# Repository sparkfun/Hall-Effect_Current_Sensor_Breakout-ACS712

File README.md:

SparkFun Current Sensor Breakout - ACS723
=====================================================

[*SparkFun Current Sensor Breakout - ACS723 (SEN-13679)*](https://www.sparkfun.com/products/13679)

This is a breakout board for the fully integrated Hall Effect based linear ACS723 current sensor. 
The sensor gives precise current measurement for both AC and DC signals.

Repository Contents
-------------------
* **/Hardware** - All Eagle design files (.brd, .sch)
* **/Production** - Production .brd files

Documentation
-------------------
[Hookup Guide](https://learn.sparkfun.com/tutorials/current-sensor-breakout-acs723-hookup-guide) - Basic hookup guide for the ACS723 Current Sensor Breakout.

Product Versions
----------------
* [SEN-13679](https://www.sparkfun.com/products/13679)- Current ACS723 Version of this Board
* [SEN-08882 (RETIRED)](https://github.com/sparkfun/Hall-Effect_Current_Sensor_Breakout-ACS712)- Initial release; ACS712 Version of this Board

License Information
-------------------

This product is _**open source**_! 

Please review the LICENSE.md file for license information. 

If you have any questions or concerns on licensing, please contact techsupport@sparkfun.com.

Distributed as-is; no warranty is given.

- Your friends at SparkFun.

_<COLLABORATION CREDIT>_

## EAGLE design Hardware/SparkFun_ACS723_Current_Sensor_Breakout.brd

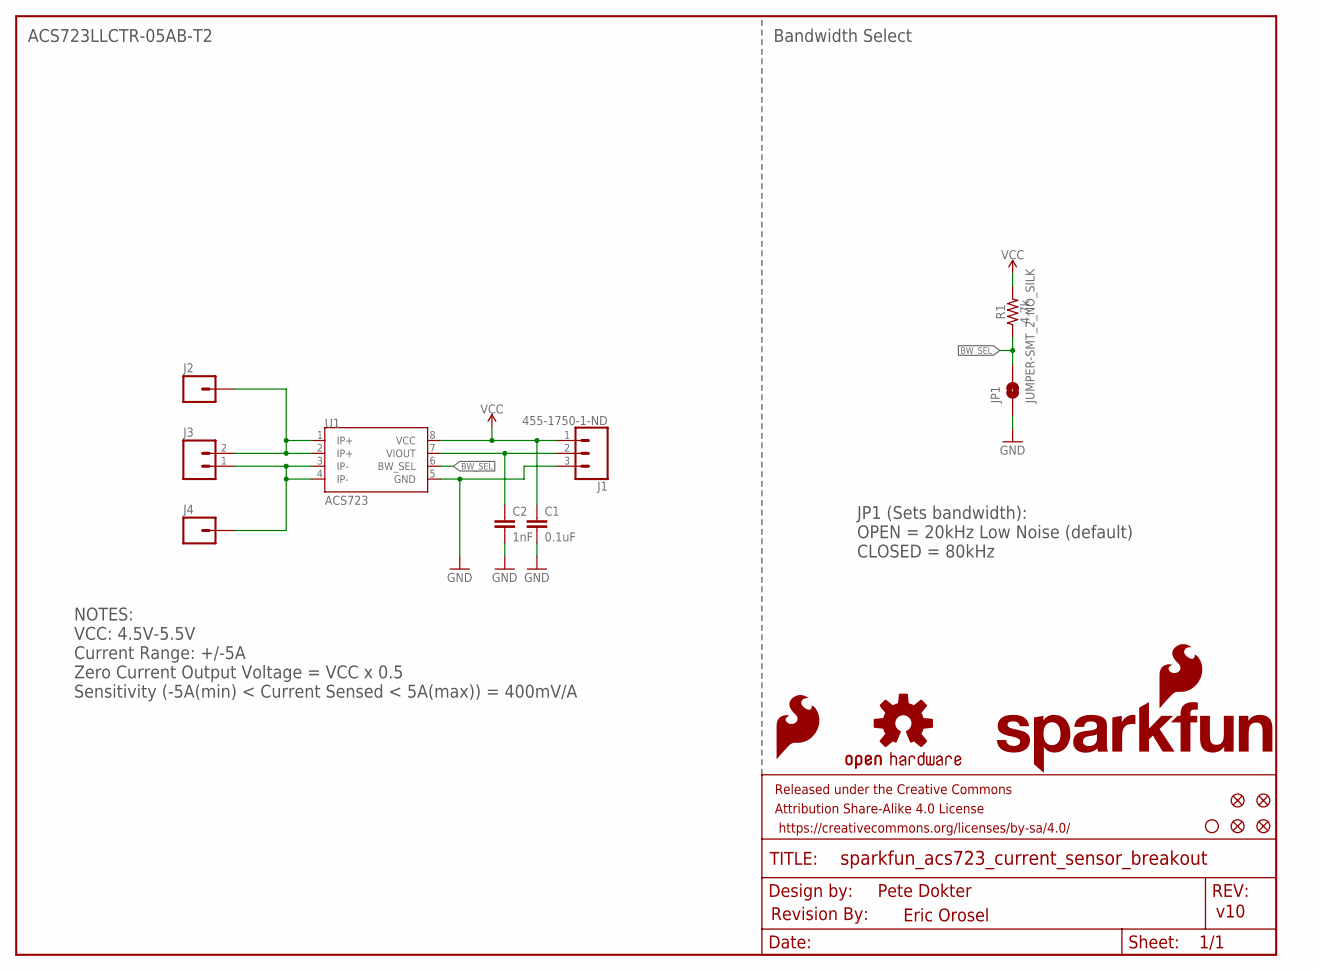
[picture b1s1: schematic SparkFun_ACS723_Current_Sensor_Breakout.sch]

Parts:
C1: 0.1uF; 0603
C2: 1nF; 0603
FD2, FD3, FD4, FD5: FIDUCIAL1X2; FIDUCIAL-1X2
FRAME1: FRAME-LETTER; CREATIVE_COMMONS
J1: 455-1750-1-ND; 1X03
J2, J4: M01-SMTSO-256-ET; SMTSO-256-ET
J3: M021X02_NO_SILK; 1X02_NO_SILK@1
JP1: JUMPER-SMT_2_NO_SILK; SMT-JUMPER_2_NO_SILK
JP3: STAND-OFFTIGHT; STAND-OFF-TIGHT
LOGO1: SFE_LOGO_FLAME.1_INCH; SFE_LOGO_FLAME_.1
LOGO3: SFE_LOGO_NAME_FLAME.1_INCH; SFE_LOGO_NAME_FLAME_.1
LOGO4: OSHW-LOGOM; OSHW-LOGO-M
R1: 4.7k; 0603
U1: ACS723; SO08
U$1: REVISION

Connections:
BW_SEL: JP1.2, R1.1, U1.6 (BW_SEL)
GND: C1.2, C2.2, J1.3, JP1.1, U1.5 (GND)
IP+: J2.P$1, J3.2, U1.1 (IP+), U1.2 (IP+)
IP-: J3.1, J4.P$1, U1.3 (IP-), U1.4 (IP-)
unnamed: C2.1, J1.2, U1.7 (VIOUT)
VCC: C1.1, J1.1, R1.2, U1.8 (VCC)

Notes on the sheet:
Pete Dokter
v10
Eric Orosel
Current Range: +/-5A
VCC: 4.5V-5.5V
JP1 (Sets bandwidth):
CLOSED = 80kHz
OPEN = 20kHz Low Noise (default)
ACS723LLCTR-05AB-T2
Bandwidth Select
Zero Current Output Voltage = VCC x 0.5
Sensitivity (-5A(min) < Current Sensed < 5A(max)) = 400mV/A
NOTES:

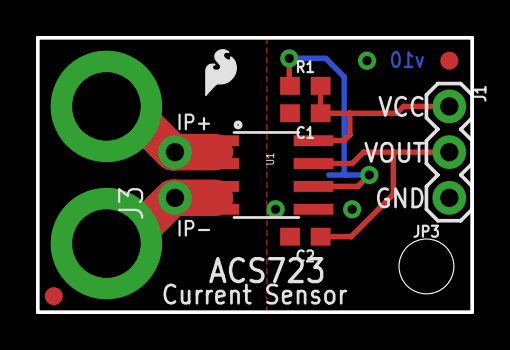
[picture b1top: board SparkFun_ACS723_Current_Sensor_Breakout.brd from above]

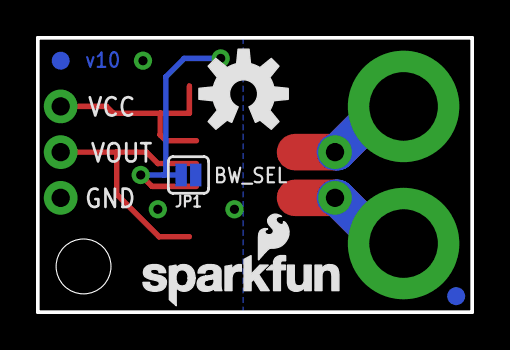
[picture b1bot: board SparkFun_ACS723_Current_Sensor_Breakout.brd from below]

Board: 2 copper layers, 24.1 x 15.2 mm, 19 parts (5 on the bottom side), 6 nets.

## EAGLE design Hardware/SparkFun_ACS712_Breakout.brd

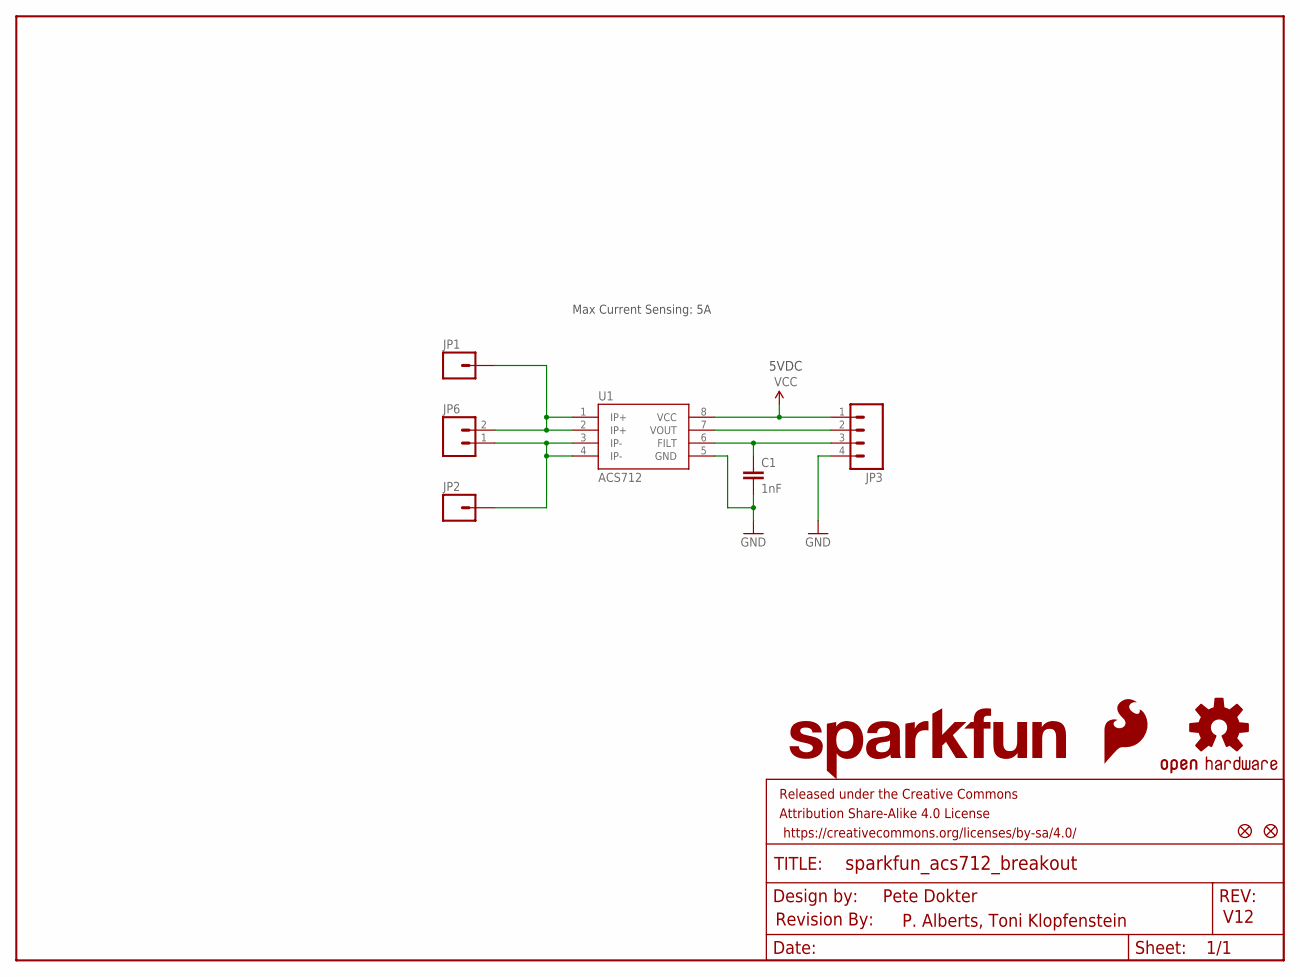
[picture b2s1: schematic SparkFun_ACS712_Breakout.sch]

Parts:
C1: 1nF; 0603-CAP
FRAME1: FRAME-LETTER; CREATIVE_COMMONS
JP1, JP2: M01-SMTSO-256-ET; SMTSO-256-ET
JP3: M04PTH; 1X04
JP4, JP5: FIDUCIALUFIDUCIAL; MICRO-FIDUCIAL
JP6: M021X02_NO_SILK; 1X02_NO_SILK
LOGO1: SFE_LOGO_NAME.1_INCH; SFE_LOGO_NAME_.1
LOGO2: SFE_LOGO_FLAME.3_INCH; SFE_LOGO_FLAME_.3
U1: ACS712; SO08
U$1: REVISION
U$3: OSHW-LOGOS; OSHW-LOGO-S

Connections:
FILT: C1.1, JP3.3, U1.6 (FILT)
GND: C1.2, JP3.4, U1.5 (GND)
IP+: JP1.P$1, JP6.2, U1.1 (IP+), U1.2 (IP+)
IP-: JP2.P$1, JP6.1, U1.3 (IP-), U1.4 (IP-)
VCC: JP3.1, U1.8 (VCC)
VOUT: JP3.2, U1.7 (VOUT)

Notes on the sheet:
Pete Dokter
V12
5VDC
P. Alberts, Toni Klopfenstein
Max Current Sensing: 5A

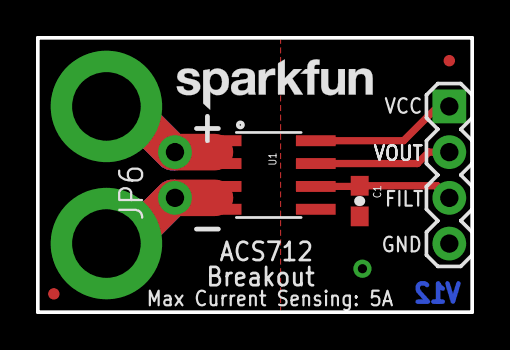
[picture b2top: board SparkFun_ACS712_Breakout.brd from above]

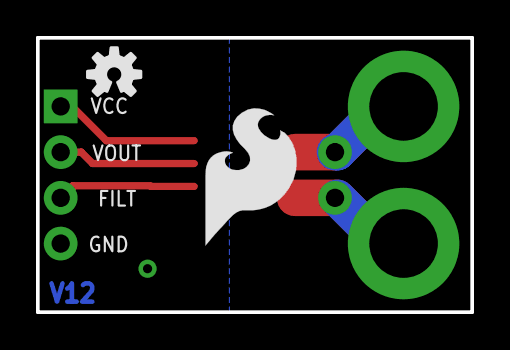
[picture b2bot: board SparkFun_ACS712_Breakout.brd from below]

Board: 2 copper layers, 24.1 x 15.2 mm, 13 parts (2 on the bottom side), 6 nets.

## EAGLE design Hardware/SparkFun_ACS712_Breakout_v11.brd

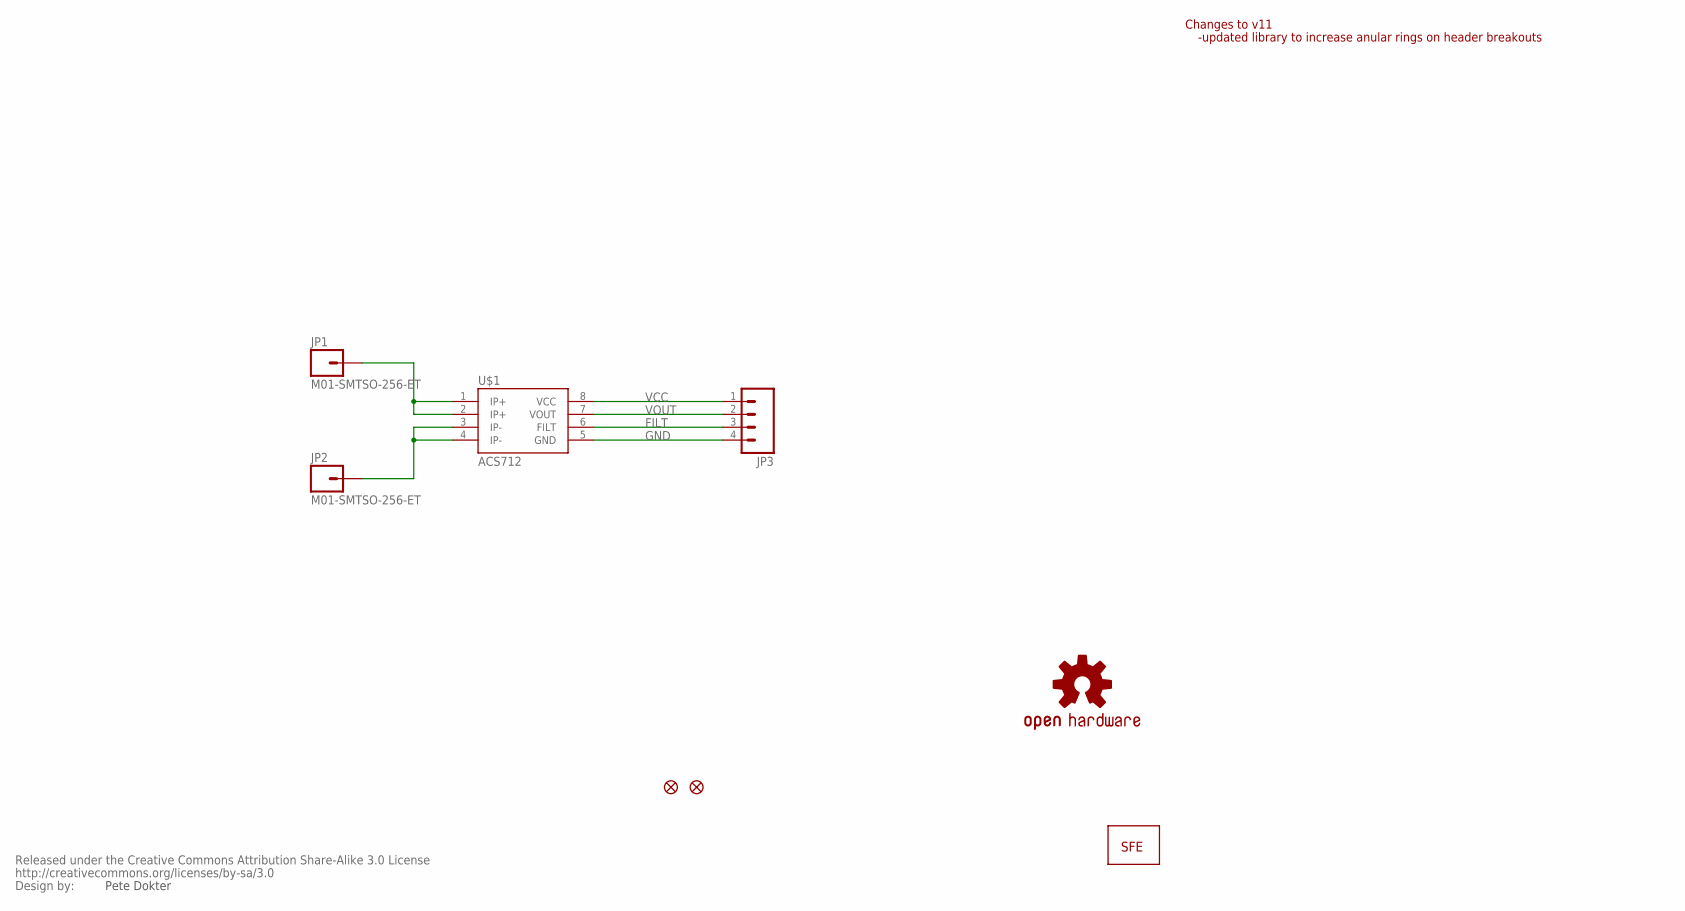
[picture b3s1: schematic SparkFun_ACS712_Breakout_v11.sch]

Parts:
JP1, JP2: M01-SMTSO-256-ET; SMTSO-256-ET
JP3: M04PTH; 1X04
JP4, JP5: FIDUCIALUFIDUCIAL; MICRO-FIDUCIAL
U$1: ACS712; SO08
U$2: LOGO-FLAME-LARGE
U$3: OSHW-LOGOS; OSHW-LOGO-S
U$4: CREATIVE_COMMONS

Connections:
FILT: JP3.3, U$1.6 (FILT)
GND: JP3.4, U$1.5 (GND)
unnamed: JP1.P$1, U$1.1 (IP+), U$1.2 (IP+)
unnamed: JP2.P$1, U$1.3 (IP-), U$1.4 (IP-)
VCC: JP3.1, U$1.8 (VCC)
VOUT: JP3.2, U$1.7 (VOUT)

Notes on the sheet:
Changes to v11
-updated library to increase anular rings on header breakouts
Pete Dokter

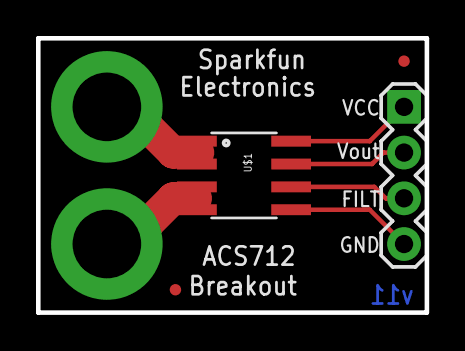
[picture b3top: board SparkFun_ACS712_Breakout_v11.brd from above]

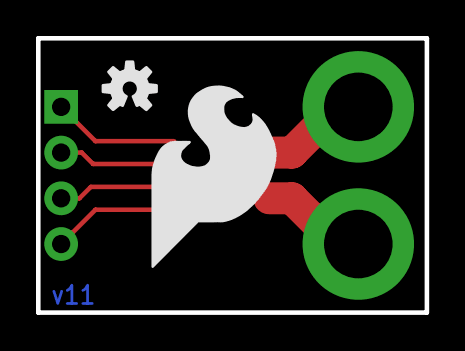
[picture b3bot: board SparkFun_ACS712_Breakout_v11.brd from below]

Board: 2 copper layers, 21.6 x 15.2 mm, 9 parts (2 on the bottom side), 6 nets.

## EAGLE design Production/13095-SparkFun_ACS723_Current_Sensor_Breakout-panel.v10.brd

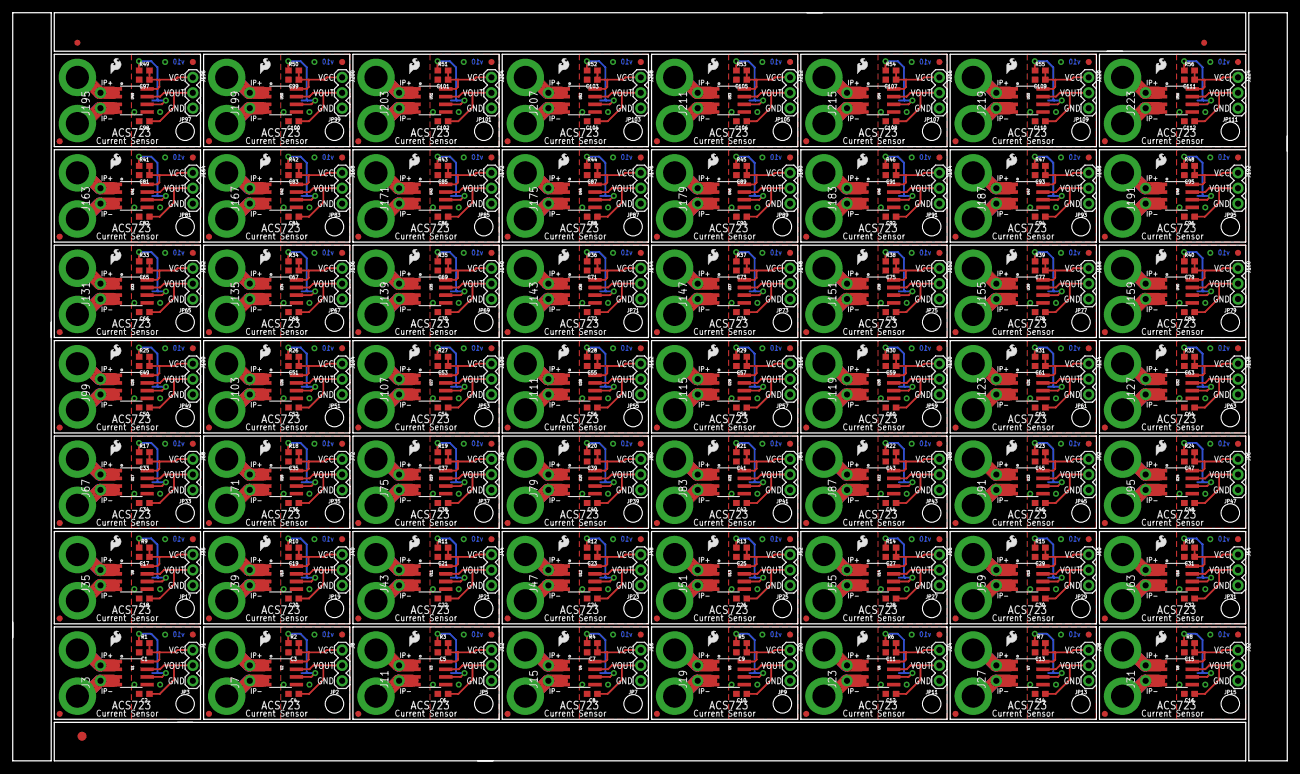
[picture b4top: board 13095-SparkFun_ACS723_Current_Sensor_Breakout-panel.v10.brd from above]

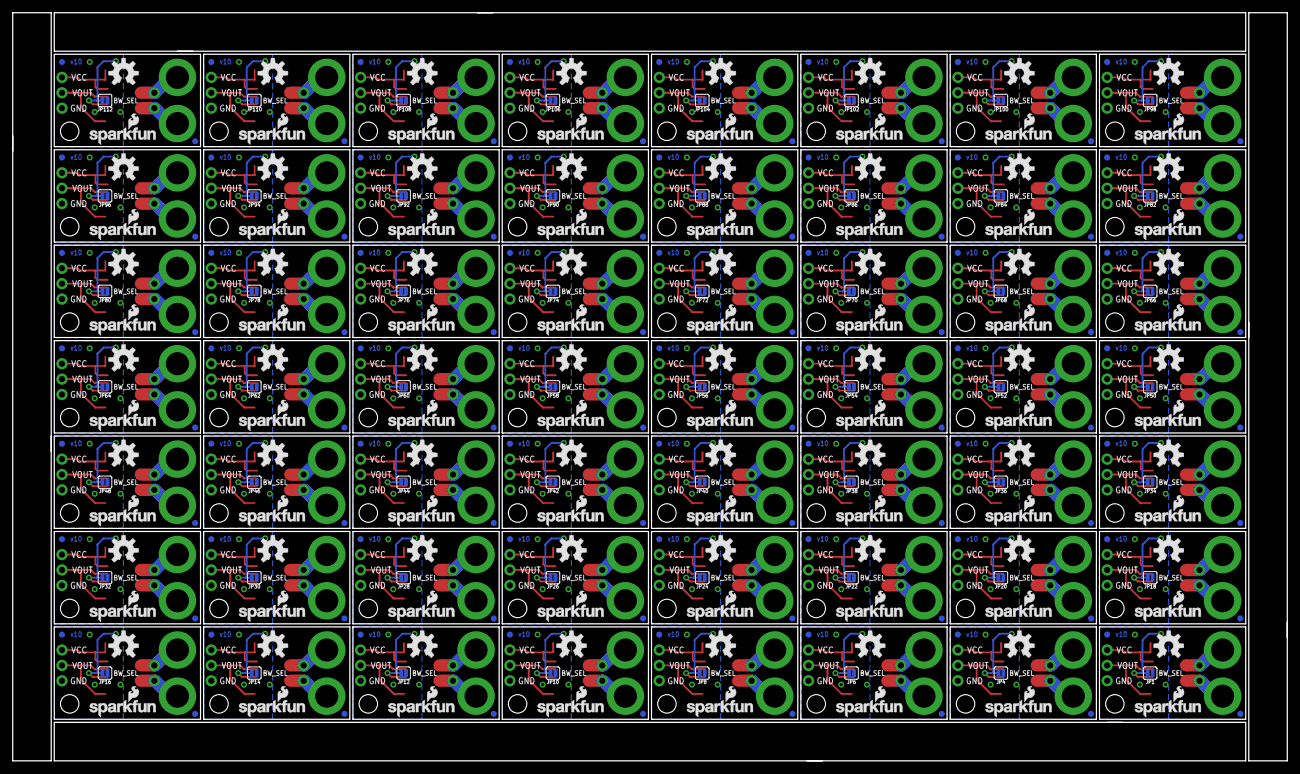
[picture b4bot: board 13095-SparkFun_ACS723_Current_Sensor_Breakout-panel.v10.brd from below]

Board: 2 copper layers, 210.3 x 123.4 mm, 955 parts (280 on the bottom side), 336 nets.

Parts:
C1, C3, C5, C7, C9, C11, C13, C15, C17, C19, C21, C23, C25, C27, C29, C31, C33, C35, C37, C39, C41, C43, C45, C47, C49, C51, C53, C55, C57, C59, C61, C63, C65, C67, C69, C71, C73, C75, C77, C79, C81, C83, C85, C87, C89, C91, C93, C95, C97, C99, C101, C103, C105, C107, C109, C111: 0.1uF; 0603
C2, C4, C6, C8, C10, C12, C14, C16, C18, C20, C22, C24, C26, C28, C30, C32, C34, C36, C38, C40, C42, C44, C46, C48, C50, C52, C54, C56, C58, C60, C62, C64, C66, C68, C70, C72, C74, C76, C78, C80, C82, C84, C86, C88, C90, C92, C94, C96, C98, C100, C102, C104, C106, C108, C110, C112: 1nF; 0603
E$1: FIDUCIAL-1.5X3
E$5, E$6: FIDUCIAL-1X2
FD1, FD2, FD3, FD4, FD5, FD6, FD7, FD8, FD9, FD10, FD11, FD12, FD13, FD14, FD15, FD16, FD17, FD18, FD19, FD20, FD21, FD22, FD23, FD24, FD25, FD26, FD27, FD28, FD29, FD30, FD31, FD32, FD33, FD34, FD35, FD36, FD37, FD38, FD39, FD40, FD41, FD42, FD43, FD44, FD45, FD46, FD47, FD48, FD49, FD50, FD51, FD52, FD53, FD54, FD55, FD56, FD57, FD58, FD59, FD60, FD61, FD62, FD63, FD64, FD65, FD66, FD67, FD68, FD69, FD70, FD71, FD72, FD73, FD74, FD75, FD76, FD77, FD78, FD79, FD80, FD81, FD82, FD83, FD84, FD85, FD86, FD87, FD88, FD89, FD90, FD91, FD92, FD93, FD94, FD95, FD96, FD97, FD98, FD99, FD100, FD101, FD102, FD103, FD104, FD105, FD106, FD107, FD108, FD109, FD110, FD111, FD112, FD113, FD114, FD115, FD116, FD117, FD118, FD119, FD120, FD121, FD122, FD123, FD124, FD125, FD126, FD127, FD128, FD129, FD130, FD131, FD132, FD133, FD134, FD135, FD136, FD137, FD138, FD139, FD140, FD141, FD142, FD143, FD144, FD145, FD146, FD147, FD148, FD149, FD150, FD151, FD152, FD153, FD154, FD155, FD156, FD157, FD158, FD159, FD160, FD161, FD162, FD163, FD164, FD165, FD166, FD167, FD168, FD169, FD170, FD171, FD172, FD173, FD174, FD175, FD176, FD177, FD178, FD179, FD180, FD181, FD182, FD183, FD184, FD185, FD186, FD187, FD188, FD189, FD190, FD191, FD192, FD193, FD194, FD195, FD196, FD197, FD198, FD199, FD200, FD201, FD202, FD203, FD204, FD205, FD206, FD207, FD208, FD209, FD210, FD211, FD212, FD213, FD214, FD215, FD216, FD217, FD218, FD219, FD220, FD221, FD222, FD223, FD224: FIDUCIAL1X2; FIDUCIAL-1X2
J1, J8, J12, J16, J20, J24, J28, J32, J36, J40, J44, J48, J52, J56, J60, J64, J68, J72, J76, J80, J84, J88, J92, J96, J100, J104, J108, J112, J116, J120, J124, J128, J132, J136, J140, J144, J148, J152, J156, J160, J164, J168, J172, J176, J180, J184, J188, J192, J196, J200, J204, J208, J212, J216, J220, J224: 455-1750-1-ND; 1X03
J2, J4, J5, J6, J9, J10, J13, J14, J17, J18, J21, J22, J25, J26, J29, J30, J33, J34, J37, J38, J41, J42, J45, J46, J49, J50, J53, J54, J57, J58, J61, J62, J65, J66, J69, J70, J73, J74, J77, J78, J81, J82, J85, J86, J89, J90, J93, J94, J97, J98, J101, J102, J105, J106, J109, J110, J113, J114, J117, J118, J121, J122, J125, J126, J129, J130, J133, J134, J137, J138, J141, J142, J145, J146, J149, J150, J153, J154, J157, J158, J161, J162, J165, J166, J169, J170, J173, J174, J177, J178, J181, J182, J185, J186, J189, J190, J193, J194, J197, J198, J201, J202, J205, J206, J209, J210, J213, J214, J217, J218, J221, J222: SMTSO-256-ET
J3, J7, J11, J15, J19, J23, J27, J31, J35, J39, J43, J47, J51, J55, J59, J63, J67, J71, J75, J79, J83, J87, J91, J95, J99, J103, J107, J111, J115, J119, J123, J127, J131, J135, J139, J143, J147, J151, J155, J159, J163, J167, J171, J175, J179, J183, J187, J191, J195, J199, J203, J207, J211, J215, J219, J223: 1X02_NO_SILK@1
JP1, JP4, JP6, JP8, JP10, JP12, JP14, JP16, JP18, JP20, JP22, JP24, JP26, JP28, JP30, JP32, JP34, JP36, JP38, JP40, JP42, JP44, JP46, JP48, JP50, JP52, JP54, JP56, JP58, JP60, JP62, JP64, JP66, JP68, JP70, JP72, JP74, JP76, JP78, JP80, JP82, JP84, JP86, JP88, JP90, JP92, JP94, JP96, JP98, JP100, JP102, JP104, JP106, JP108, JP110, JP112: JUMPER-SMT_2_NO_SILK; SMT-JUMPER_2_NO_SILK
JP2, JP3, JP5, JP7, JP9, JP11, JP13, JP15, JP17, JP19, JP21, JP23, JP25, JP27, JP29, JP31, JP33, JP35, JP37, JP39, JP41, JP43, JP45, JP47, JP49, JP51, JP53, JP55, JP57, JP59, JP61, JP63, JP65, JP67, JP69, JP71, JP73, JP75, JP77, JP79, JP81, JP83, JP85, JP87, JP89, JP91, JP93, JP95, JP97, JP99, JP101, JP103, JP105, JP107, JP109, JP111: STAND-OFFTIGHT; STAND-OFF-TIGHT
LOGO1, LOGO2, LOGO7, LOGO10, LOGO13, LOGO16, LOGO19, LOGO22, LOGO25, LOGO28, LOGO31, LOGO34, LOGO37, LOGO40, LOGO43, LOGO46, LOGO49, LOGO52, LOGO55, LOGO58, LOGO61, LOGO64, LOGO67, LOGO70, LOGO73, LOGO76, LOGO79, LOGO82, LOGO85, LOGO88, LOGO91, LOGO94, LOGO97, LOGO100, LOGO103, LOGO106, LOGO109, LOGO112, LOGO115, LOGO118, LOGO121, LOGO124, LOGO127, LOGO130, LOGO133, LOGO136, LOGO139, LOGO142, LOGO145, LOGO148, LOGO151, LOGO154, LOGO157, LOGO160, LOGO163, LOGO166: SFE_LOGO_FLAME.1_INCH; SFE_LOGO_FLAME_.1
LOGO3, LOGO5, LOGO8, LOGO11, LOGO14, LOGO17, LOGO20, LOGO23, LOGO26, LOGO29, LOGO32, LOGO35, LOGO38, LOGO41, LOGO44, LOGO47, LOGO50, LOGO53, LOGO56, LOGO59, LOGO62, LOGO65, LOGO68, LOGO71, LOGO74, LOGO77, LOGO80, LOGO83, LOGO86, LOGO89, LOGO92, LOGO95, LOGO98, LOGO101, LOGO104, LOGO107, LOGO110, LOGO113, LOGO116, LOGO119, LOGO122, LOGO125, LOGO128, LOGO131, LOGO134, LOGO137, LOGO140, LOGO143, LOGO146, LOGO149, LOGO152, LOGO155, LOGO158, LOGO161, LOGO164, LOGO167: SFE_LOGO_NAME_FLAME.1_INCH; SFE_LOGO_NAME_FLAME_.1
LOGO4, LOGO6, LOGO9, LOGO12, LOGO15, LOGO18, LOGO21, LOGO24, LOGO27, LOGO30, LOGO33, LOGO36, LOGO39, LOGO42, LOGO45, LOGO48, LOGO51, LOGO54, LOGO57, LOGO60, LOGO63, LOGO66, LOGO69, LOGO72, LOGO75, LOGO78, LOGO81, LOGO84, LOGO87, LOGO90, LOGO93, LOGO96, LOGO99, LOGO102, LOGO105, LOGO108, LOGO111, LOGO114, LOGO117, LOGO120, LOGO123, LOGO126, LOGO129, LOGO132, LOGO135, LOGO138, LOGO141, LOGO144, LOGO147, LOGO150, LOGO153, LOGO156, LOGO159, LOGO162, LOGO165, LOGO168: OSHW-LOGOM; OSHW-LOGO-M
R1, R2, R3, R4, R5, R6, R7, R8, R9, R10, R11, R12, R13, R14, R15, R16, R17, R18, R19, R20, R21, R22, R23, R24, R25, R26, R27, R28, R29, R30, R31, R32, R33, R34, R35, R36, R37, R38, R39, R40, R41, R42, R43, R44, R45, R46, R47, R48, R49, R50, R51, R52, R53, R54, R55, R56: 4.7k; 0603
U1, U2, U3, U4, U5, U6, U7, U8, U9, U10, U11, U12, U13, U14, U15, U16, U17, U18, U19, U20, U21, U22, U23, U24, U25, U26, U27, U28, U29, U30, U31, U32, U33, U34, U35, U36, U37, U38, U39, U40, U41, U42, U43, U44, U45, U46, U47, U48, U49, U50, U51, U52, U53, U54, U55, U56: ACS723; SO08

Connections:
BW_SEL: JP1.2, R1.1, U1.6
BW_SEL1: JP4.2, R2.1, U2.6
BW_SEL2: JP6.2, R3.1, U3.6
BW_SEL3: JP8.2, R4.1, U4.6
BW_SEL4: JP10.2, R5.1, U5.6
BW_SEL5: JP12.2, R6.1, U6.6
BW_SEL6: JP14.2, R7.1, U7.6
BW_SEL7: JP16.2, R8.1, U8.6
BW_SEL8: JP18.2, R9.1, U9.6
BW_SEL9: JP20.2, R10.1, U10.6
BW_SEL10: JP22.2, R11.1, U11.6
BW_SEL11: JP24.2, R12.1, U12.6
BW_SEL12: JP26.2, R13.1, U13.6
BW_SEL13: JP28.2, R14.1, U14.6
BW_SEL14: JP30.2, R15.1, U15.6
BW_SEL15: JP32.2, R16.1, U16.6
BW_SEL16: JP34.2, R17.1, U17.6
BW_SEL17: JP36.2, R18.1, U18.6
BW_SEL18: JP38.2, R19.1, U19.6
BW_SEL19: JP40.2, R20.1, U20.6
BW_SEL20: JP42.2, R21.1, U21.6
BW_SEL21: JP44.2, R22.1, U22.6
BW_SEL22: JP46.2, R23.1, U23.6
BW_SEL23: JP48.2, R24.1, U24.6
BW_SEL24: JP50.2, R25.1, U25.6
BW_SEL25: JP52.2, R26.1, U26.6
BW_SEL26: JP54.2, R27.1, U27.6
BW_SEL27: JP56.2, R28.1, U28.6
BW_SEL28: JP58.2, R29.1, U29.6
BW_SEL29: JP60.2, R30.1, U30.6
BW_SEL30: JP62.2, R31.1, U31.6
BW_SEL31: JP64.2, R32.1, U32.6
BW_SEL32: JP66.2, R33.1, U33.6
BW_SEL33: JP68.2, R34.1, U34.6
BW_SEL34: JP70.2, R35.1, U35.6
BW_SEL35: JP72.2, R36.1, U36.6
BW_SEL36: JP74.2, R37.1, U37.6
BW_SEL37: JP76.2, R38.1, U38.6
BW_SEL38: JP78.2, R39.1, U39.6
BW_SEL39: JP80.2, R40.1, U40.6
BW_SEL40: JP82.2, R41.1, U41.6
BW_SEL41: JP84.2, R42.1, U42.6
BW_SEL42: JP86.2, R43.1, U43.6
BW_SEL43: JP88.2, R44.1, U44.6
BW_SEL44: JP90.2, R45.1, U45.6
BW_SEL45: JP92.2, R46.1, U46.6
BW_SEL46: JP94.2, R47.1, U47.6
BW_SEL47: JP96.2, R48.1, U48.6
BW_SEL48: JP98.2, R49.1, U49.6
BW_SEL49: JP100.2, R50.1, U50.6
BW_SEL50: JP102.2, R51.1, U51.6
BW_SEL51: JP104.2, R52.1, U52.6
BW_SEL52: JP106.2, R53.1, U53.6
BW_SEL53: JP108.2, R54.1, U54.6
BW_SEL54: JP110.2, R55.1, U55.6
BW_SEL55: JP112.2, R56.1, U56.6
GND: C1.2, C2.2, J1.3, JP1.1, U1.5
GND1: C3.2, C4.2, J8.3, JP4.1, U2.5
GND2: C5.2, C6.2, J12.3, JP6.1, U3.5
GND3: C7.2, C8.2, J16.3, JP8.1, U4.5
GND4: C9.2, C10.2, J20.3, JP10.1, U5.5
GND5: C11.2, C12.2, J24.3, JP12.1, U6.5
GND6: C13.2, C14.2, J28.3, JP14.1, U7.5
GND7: C15.2, C16.2, J32.3, JP16.1, U8.5
GND8: C17.2, C18.2, J36.3, JP18.1, U9.5
GND9: C19.2, C20.2, J40.3, JP20.1, U10.5
GND10: C21.2, C22.2, J44.3, JP22.1, U11.5
GND11: C23.2, C24.2, J48.3, JP24.1, U12.5
GND12: C25.2, C26.2, J52.3, JP26.1, U13.5
GND13: C27.2, C28.2, J56.3, JP28.1, U14.5
GND14: C29.2, C30.2, J60.3, JP30.1, U15.5
GND15: C31.2, C32.2, J64.3, JP32.1, U16.5
GND16: C33.2, C34.2, J68.3, JP34.1, U17.5
GND17: C35.2, C36.2, J72.3, JP36.1, U18.5
GND18: C37.2, C38.2, J76.3, JP38.1, U19.5
GND19: C39.2, C40.2, J80.3, JP40.1, U20.5
GND20: C41.2, C42.2, J84.3, JP42.1, U21.5
GND21: C43.2, C44.2, J88.3, JP44.1, U22.5
GND22: C45.2, C46.2, J92.3, JP46.1, U23.5
GND23: C47.2, C48.2, J96.3, JP48.1, U24.5
GND24: C49.2, C50.2, J100.3, JP50.1, U25.5
GND25: C51.2, C52.2, J104.3, JP52.1, U26.5
GND26: C53.2, C54.2, J108.3, JP54.1, U27.5
GND27: C55.2, C56.2, J112.3, JP56.1, U28.5
GND28: C57.2, C58.2, J116.3, JP58.1, U29.5
GND29: C59.2, C60.2, J120.3, JP60.1, U30.5
GND30: C61.2, C62.2, J124.3, JP62.1, U31.5
GND31: C63.2, C64.2, J128.3, JP64.1, U32.5
GND32: C65.2, C66.2, J132.3, JP66.1, U33.5
GND33: C67.2, C68.2, J136.3, JP68.1, U34.5
GND34: C69.2, C70.2, J140.3, JP70.1, U35.5
GND35: C71.2, C72.2, J144.3, JP72.1, U36.5
GND36: C73.2, C74.2, J148.3, JP74.1, U37.5
GND37: C75.2, C76.2, J152.3, JP76.1, U38.5
GND38: C77.2, C78.2, J156.3, JP78.1, U39.5
GND39: C79.2, C80.2, J160.3, JP80.1, U40.5
GND40: C81.2, C82.2, J164.3, JP82.1, U41.5
GND41: C83.2, C84.2, J168.3, JP84.1, U42.5
GND42: C85.2, C86.2, J172.3, JP86.1, U43.5
GND43: C87.2, C88.2, J176.3, JP88.1, U44.5
GND44: C89.2, C90.2, J180.3, JP90.1, U45.5
GND45: C91.2, C92.2, J184.3, JP92.1, U46.5
GND46: C93.2, C94.2, J188.3, JP94.1, U47.5
GND47: C95.2, C96.2, J192.3, JP96.1, U48.5
GND48: C97.2, C98.2, J196.3, JP98.1, U49.5
GND49: C99.2, C100.2, J200.3, JP100.1, U50.5
GND50: C101.2, C102.2, J204.3, JP102.1, U51.5
GND51: C103.2, C104.2, J208.3, JP104.1, U52.5
GND52: C105.2, C106.2, J212.3, JP106.1, U53.5
GND53: C107.2, C108.2, J216.3, JP108.1, U54.5
GND54: C109.2, C110.2, J220.3, JP110.1, U55.5
GND55: C111.2, C112.2, J224.3, JP112.1, U56.5
IP+: J2.P$1, J3.2, U1.1, U1.2
IP+1: J5.P$1, J7.2, U2.1, U2.2
IP+2: J9.P$1, J11.2, U3.1, U3.2
IP+3: J13.P$1, J15.2, U4.1, U4.2
IP+4: J17.P$1, J19.2, U5.1, U5.2
IP+5: J21.P$1, J23.2, U6.1, U6.2
IP+6: J25.P$1, J27.2, U7.1, U7.2
IP+7: J29.P$1, J31.2, U8.1, U8.2
IP+8: J33.P$1, J35.2, U9.1, U9.2
IP+9: J37.P$1, J39.2, U10.1, U10.2
IP+10: J41.P$1, J43.2, U11.1, U11.2
IP+11: J45.P$1, J47.2, U12.1, U12.2
IP+12: J49.P$1, J51.2, U13.1, U13.2
IP+13: J53.P$1, J55.2, U14.1, U14.2
IP+14: J57.P$1, J59.2, U15.1, U15.2
IP+15: J61.P$1, J63.2, U16.1, U16.2
IP+16: J65.P$1, J67.2, U17.1, U17.2
IP+17: J69.P$1, J71.2, U18.1, U18.2
IP+18: J73.P$1, J75.2, U19.1, U19.2
IP+19: J77.P$1, J79.2, U20.1, U20.2
IP+20: J81.P$1, J83.2, U21.1, U21.2
IP+21: J85.P$1, J87.2, U22.1, U22.2
IP+22: J89.P$1, J91.2, U23.1, U23.2
IP+23: J93.P$1, J95.2, U24.1, U24.2
IP+24: J97.P$1, J99.2, U25.1, U25.2
IP+25: J101.P$1, J103.2, U26.1, U26.2
IP+26: J105.P$1, J107.2, U27.1, U27.2
IP+27: J109.P$1, J111.2, U28.1, U28.2
IP+28: J113.P$1, J115.2, U29.1, U29.2
IP+29: J117.P$1, J119.2, U30.1, U30.2
IP+30: J121.P$1, J123.2, U31.1, U31.2
IP+31: J125.P$1, J127.2, U32.1, U32.2
IP+32: J129.P$1, J131.2, U33.1, U33.2
IP+33: J133.P$1, J135.2, U34.1, U34.2
IP+34: J137.P$1, J139.2, U35.1, U35.2
IP+35: J141.P$1, J143.2, U36.1, U36.2
IP+36: J145.P$1, J147.2, U37.1, U37.2
IP+37: J149.P$1, J151.2, U38.1, U38.2
IP+38: J153.P$1, J155.2, U39.1, U39.2
IP+39: J157.P$1, J159.2, U40.1, U40.2
IP+40: J161.P$1, J163.2, U41.1, U41.2
IP+41: J165.P$1, J167.2, U42.1, U42.2
IP+42: J169.P$1, J171.2, U43.1, U43.2
IP+43: J173.P$1, J175.2, U44.1, U44.2
IP+44: J177.P$1, J179.2, U45.1, U45.2
IP+45: J181.P$1, J183.2, U46.1, U46.2
IP+46: J185.P$1, J187.2, U47.1, U47.2
IP+47: J189.P$1, J191.2, U48.1, U48.2
IP+48: J193.P$1, J195.2, U49.1, U49.2
IP+49: J197.P$1, J199.2, U50.1, U50.2
IP+50: J201.P$1, J203.2, U51.1, U51.2
IP+51: J205.P$1, J207.2, U52.1, U52.2
IP+52: J209.P$1, J211.2, U53.1, U53.2
IP+53: J213.P$1, J215.2, U54.1, U54.2
IP+54: J217.P$1, J219.2, U55.1, U55.2
IP+55: J221.P$1, J223.2, U56.1, U56.2
IP-: J3.1, J4.P$1, U1.3, U1.4
IP-1: J6.P$1, J7.1, U2.3, U2.4
IP-2: J10.P$1, J11.1, U3.3, U3.4
IP-3: J14.P$1, J15.1, U4.3, U4.4
IP-4: J18.P$1, J19.1, U5.3, U5.4
IP-5: J22.P$1, J23.1, U6.3, U6.4
IP-6: J26.P$1, J27.1, U7.3, U7.4
IP-7: J30.P$1, J31.1, U8.3, U8.4
IP-8: J34.P$1, J35.1, U9.3, U9.4
IP-9: J38.P$1, J39.1, U10.3, U10.4
IP-10: J42.P$1, J43.1, U11.3, U11.4
IP-11: J46.P$1, J47.1, U12.3, U12.4
IP-12: J50.P$1, J51.1, U13.3, U13.4
IP-13: J54.P$1, J55.1, U14.3, U14.4
IP-14: J58.P$1, J59.1, U15.3, U15.4
IP-15: J62.P$1, J63.1, U16.3, U16.4
IP-16: J66.P$1, J67.1, U17.3, U17.4
IP-17: J70.P$1, J71.1, U18.3, U18.4
IP-18: J74.P$1, J75.1, U19.3, U19.4
IP-19: J78.P$1, J79.1, U20.3, U20.4
IP-20: J82.P$1, J83.1, U21.3, U21.4
IP-21: J86.P$1, J87.1, U22.3, U22.4
IP-22: J90.P$1, J91.1, U23.3, U23.4
IP-23: J94.P$1, J95.1, U24.3, U24.4
IP-24: J98.P$1, J99.1, U25.3, U25.4
IP-25: J102.P$1, J103.1, U26.3, U26.4
IP-26: J106.P$1, J107.1, U27.3, U27.4
IP-27: J110.P$1, J111.1, U28.3, U28.4
IP-28: J114.P$1, J115.1, U29.3, U29.4
IP-29: J118.P$1, J119.1, U30.3, U30.4
IP-30: J122.P$1, J123.1, U31.3, U31.4
IP-31: J126.P$1, J127.1, U32.3, U32.4
IP-32: J130.P$1, J131.1, U33.3, U33.4
IP-33: J134.P$1, J135.1, U34.3, U34.4
IP-34: J138.P$1, J139.1, U35.3, U35.4
IP-35: J142.P$1, J143.1, U36.3, U36.4
IP-36: J146.P$1, J147.1, U37.3, U37.4
IP-37: J150.P$1, J151.1, U38.3, U38.4
IP-38: J154.P$1, J155.1, U39.3, U39.4
IP-39: J158.P$1, J159.1, U40.3, U40.4
IP-40: J162.P$1, J163.1, U41.3, U41.4
IP-41: J166.P$1, J167.1, U42.3, U42.4
IP-42: J170.P$1, J171.1, U43.3, U43.4
IP-43: J174.P$1, J175.1, U44.3, U44.4
IP-44: J178.P$1, J179.1, U45.3, U45.4
IP-45: J182.P$1, J183.1, U46.3, U46.4
IP-46: J186.P$1, J187.1, U47.3, U47.4
IP-47: J190.P$1, J191.1, U48.3, U48.4
IP-48: J194.P$1, J195.1, U49.3, U49.4
IP-49: J198.P$1, J199.1, U50.3, U50.4
IP-50: J202.P$1, J203.1, U51.3, U51.4
IP-51: J206.P$1, J207.1, U52.3, U52.4
IP-52: J210.P$1, J211.1, U53.3, U53.4
IP-53: J214.P$1, J215.1, U54.3, U54.4
IP-54: J218.P$1, J219.1, U55.3, U55.4
IP-55: J222.P$1, J223.1, U56.3, U56.4
unnamed: C2.1, J1.2, U1.7
unnamed: C4.1, J8.2, U2.7
unnamed: C6.1, J12.2, U3.7
unnamed: C8.1, J16.2, U4.7
unnamed: C10.1, J20.2, U5.7
unnamed: C12.1, J24.2, U6.7
unnamed: C14.1, J28.2, U7.7
unnamed: C16.1, J32.2, U8.7
unnamed: C18.1, J36.2, U9.7
unnamed: C20.1, J40.2, U10.7
unnamed: C22.1, J44.2, U11.7
unnamed: C24.1, J48.2, U12.7
unnamed: C26.1, J52.2, U13.7
unnamed: C28.1, J56.2, U14.7
unnamed: C30.1, J60.2, U15.7
unnamed: C32.1, J64.2, U16.7
unnamed: C34.1, J68.2, U17.7
unnamed: C36.1, J72.2, U18.7
unnamed: C38.1, J76.2, U19.7
unnamed: C40.1, J80.2, U20.7
unnamed: C42.1, J84.2, U21.7
unnamed: C44.1, J88.2, U22.7
unnamed: C46.1, J92.2, U23.7
unnamed: C48.1, J96.2, U24.7
unnamed: C50.1, J100.2, U25.7
unnamed: C52.1, J104.2, U26.7
unnamed: C54.1, J108.2, U27.7
unnamed: C56.1, J112.2, U28.7
unnamed: C58.1, J116.2, U29.7
unnamed: C60.1, J120.2, U30.7
unnamed: C62.1, J124.2, U31.7
unnamed: C64.1, J128.2, U32.7
unnamed: C66.1, J132.2, U33.7
unnamed: C68.1, J136.2, U34.7
unnamed: C70.1, J140.2, U35.7
unnamed: C72.1, J144.2, U36.7
unnamed: C74.1, J148.2, U37.7
unnamed: C76.1, J152.2, U38.7
unnamed: C78.1, J156.2, U39.7
unnamed: C80.1, J160.2, U40.7
unnamed: C82.1, J164.2, U41.7
unnamed: C84.1, J168.2, U42.7
unnamed: C86.1, J172.2, U43.7
unnamed: C88.1, J176.2, U44.7
unnamed: C90.1, J180.2, U45.7
unnamed: C92.1, J184.2, U46.7
unnamed: C94.1, J188.2, U47.7
unnamed: C96.1, J192.2, U48.7
unnamed: C98.1, J196.2, U49.7
unnamed: C100.1, J200.2, U50.7
unnamed: C102.1, J204.2, U51.7
unnamed: C104.1, J208.2, U52.7
unnamed: C106.1, J212.2, U53.7
unnamed: C108.1, J216.2, U54.7
unnamed: C110.1, J220.2, U55.7
unnamed: C112.1, J224.2, U56.7
VCC: C1.1, J1.1, R1.2, U1.8
VCC1: C3.1, J8.1, R2.2, U2.8
VCC2: C5.1, J12.1, R3.2, U3.8
VCC3: C7.1, J16.1, R4.2, U4.8
VCC4: C9.1, J20.1, R5.2, U5.8
VCC5: C11.1, J24.1, R6.2, U6.8
VCC6: C13.1, J28.1, R7.2, U7.8
VCC7: C15.1, J32.1, R8.2, U8.8
VCC8: C17.1, J36.1, R9.2, U9.8
VCC9: C19.1, J40.1, R10.2, U10.8
VCC10: C21.1, J44.1, R11.2, U11.8
VCC11: C23.1, J48.1, R12.2, U12.8
VCC12: C25.1, J52.1, R13.2, U13.8
VCC13: C27.1, J56.1, R14.2, U14.8
VCC14: C29.1, J60.1, R15.2, U15.8
VCC15: C31.1, J64.1, R16.2, U16.8
VCC16: C33.1, J68.1, R17.2, U17.8
VCC17: C35.1, J72.1, R18.2, U18.8
VCC18: C37.1, J76.1, R19.2, U19.8
VCC19: C39.1, J80.1, R20.2, U20.8
VCC20: C41.1, J84.1, R21.2, U21.8
VCC21: C43.1, J88.1, R22.2, U22.8
VCC22: C45.1, J92.1, R23.2, U23.8
VCC23: C47.1, J96.1, R24.2, U24.8
VCC24: C49.1, J100.1, R25.2, U25.8
VCC25: C51.1, J104.1, R26.2, U26.8
VCC26: C53.1, J108.1, R27.2, U27.8
VCC27: C55.1, J112.1, R28.2, U28.8
VCC28: C57.1, J116.1, R29.2, U29.8
VCC29: C59.1, J120.1, R30.2, U30.8
VCC30: C61.1, J124.1, R31.2, U31.8
VCC31: C63.1, J128.1, R32.2, U32.8
VCC32: C65.1, J132.1, R33.2, U33.8
VCC33: C67.1, J136.1, R34.2, U34.8
VCC34: C69.1, J140.1, R35.2, U35.8
VCC35: C71.1, J144.1, R36.2, U36.8
VCC36: C73.1, J148.1, R37.2, U37.8
VCC37: C75.1, J152.1, R38.2, U38.8
VCC38: C77.1, J156.1, R39.2, U39.8
VCC39: C79.1, J160.1, R40.2, U40.8
VCC40: C81.1, J164.1, R41.2, U41.8
VCC41: C83.1, J168.1, R42.2, U42.8
VCC42: C85.1, J172.1, R43.2, U43.8
VCC43: C87.1, J176.1, R44.2, U44.8
VCC44: C89.1, J180.1, R45.2, U45.8
VCC45: C91.1, J184.1, R46.2, U46.8
VCC46: C93.1, J188.1, R47.2, U47.8
VCC47: C95.1, J192.1, R48.2, U48.8
VCC48: C97.1, J196.1, R49.2, U49.8
VCC49: C99.1, J200.1, R50.2, U50.8
VCC50: C101.1, J204.1, R51.2, U51.8
VCC51: C103.1, J208.1, R52.2, U52.8
VCC52: C105.1, J212.1, R53.2, U53.8
VCC53: C107.1, J216.1, R54.2, U54.8
VCC54: C109.1, J220.1, R55.2, U55.8
VCC55: C111.1, J224.1, R56.2, U56.8

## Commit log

2015-03-11 Adding hardware files, updating README
2015-04-22 Added headers, and 1nF cap.
2015-04-28 Fixed ENG Github Issues
2015-05-01 Fixed sch
2015-05-01 Fixed Silk
2015-05-06 Fixed qc issues
2015-05-07 Upped Trace width, fixed grid issue
    upped to 90 mil
    bo headers and sense headers are now on grid
2015-05-14 Added max current silk.
2015-07-02 A few more QC clean ups
2015-07-06 Silk fix
2015-07-28 Adding second trace on bottom layer
2017-11-09 removed old design and started new design
2017-11-14 Finalizing v01 hardware
    -Adjusted silk
    -Isolated high current side of the board
    -added recommended filter caps
    -added band-width select jumper
    -changed version number
    -changed chip package to ACS723
2017-11-21 added a couple vias for GND flow
2017-11-27 Rerouting on brd
    -Moved ground vias
    -moved passives aroun
    -rerouted some traces
2017-11-27 rerouted viout trace
2017-11-30 finalizing v01 design
    -isolated GND plane
    -added 1nf decoupling cap to viout
    -updated to 0603 footprints
    -added bandwidth select jumper
2017-12-05 Added designer attributes
    -Added "designed by" and "Revised by" attributes and frame
2017-12-05 GND plane adjustment
    -pulled GND plane 25 mil farther away from IP legs
2017-12-07 Post Eng. Review changes
    -added standoff
    -removed BW_SEL through-hole
    -moved some silk around
2017-12-08 final touches for checklist
    -moved silk
    -moved headers so they're on 100mil grid
    - Added measures
2017-12-11 v01 Proto checklist issues fixed
    -added BW_SEL note in SCH
    -Removed redundant via by GND through-hole
2017-12-29 changes after v01
    -adjusted pin label font form 32mil to 40mil
    -changed standoff to a part that lives in the sparkfun-hardware lbr
    -adjusted some spacing on silk labels
2018-01-31 v01 to v10 finalization
    -added notes for bandwidth select
    -added full IC name
    -added small info partition in sch
    -changed version numbers from v01 to v10
2018-01-31 changed product name to omit version number
    -changed name to omit version number
2018-02-05 removed old design files
2018-02-05 removed layer 2-15
2018-02-05 REMOVED LAYERS 227-231
2018-02-05 activating proper layers for viewing
2018-02-08 panel

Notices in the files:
parts and their libraries:
SparkFun-Aesthetics: Licensing: Creative Commons ShareAlike 4.0 International - https://creativecommons.org/licenses/by-sa/4.0
SparkFun-Aesthetics: Released under the Creative Commons Attribution Share-Alike 4.0 License
SparkFun-Aesthetics: https://creativecommons.org/licenses/by-sa/4.0
